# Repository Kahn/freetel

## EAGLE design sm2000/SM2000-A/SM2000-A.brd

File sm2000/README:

README for SM1000 Project
Rick Barnich KA8BMA and David Rowe VK5DGR 
Created 14 August 2014

Introduction
------------

The SM1000 is an embedded hardware product that allows you to run
FreeDV without a PC. Just plug it into your SSB or FM radio, and you
now have Digital Voice (DV). It’s based on a STM32F4 micro-controller,
has a built in microphone, speaker amplifier, and transformer isolated
interfaces to your radio. It’s about the size of a smart phone, and
can be held in you hand and used like a regular PTT microphone, or sit
near your radio in a small box. SmartMic is slated for production
production in 2014 and will retail for US$195.

The SM1000 is open hardware (TAPR license) and runs open software
(LGPL license).

Notes
------

The original name for the project was SmartMic.  However as this name
is tradmarked in the USA we are now calling the project "the
SM1000".

The SM1000 schematic and PCB are design using Eagle.

The firmware lives in codec-dev/stm32.

Directories
-----------

doc         Documentation, use cases, block diagram, prototype assembly images
SM1000-A    First pass design that was never manufactured but used to collect
            review comment
SM1000-B    Prototype SM1000, small qty of PCBs made and hand loaded
SM1000-C    pre-Beta SM1000. Changes to B to reflect testing / debug process.
            Just 2 made to check changes before Qty 100 beta run.
SM1000-D    Beta SM1000

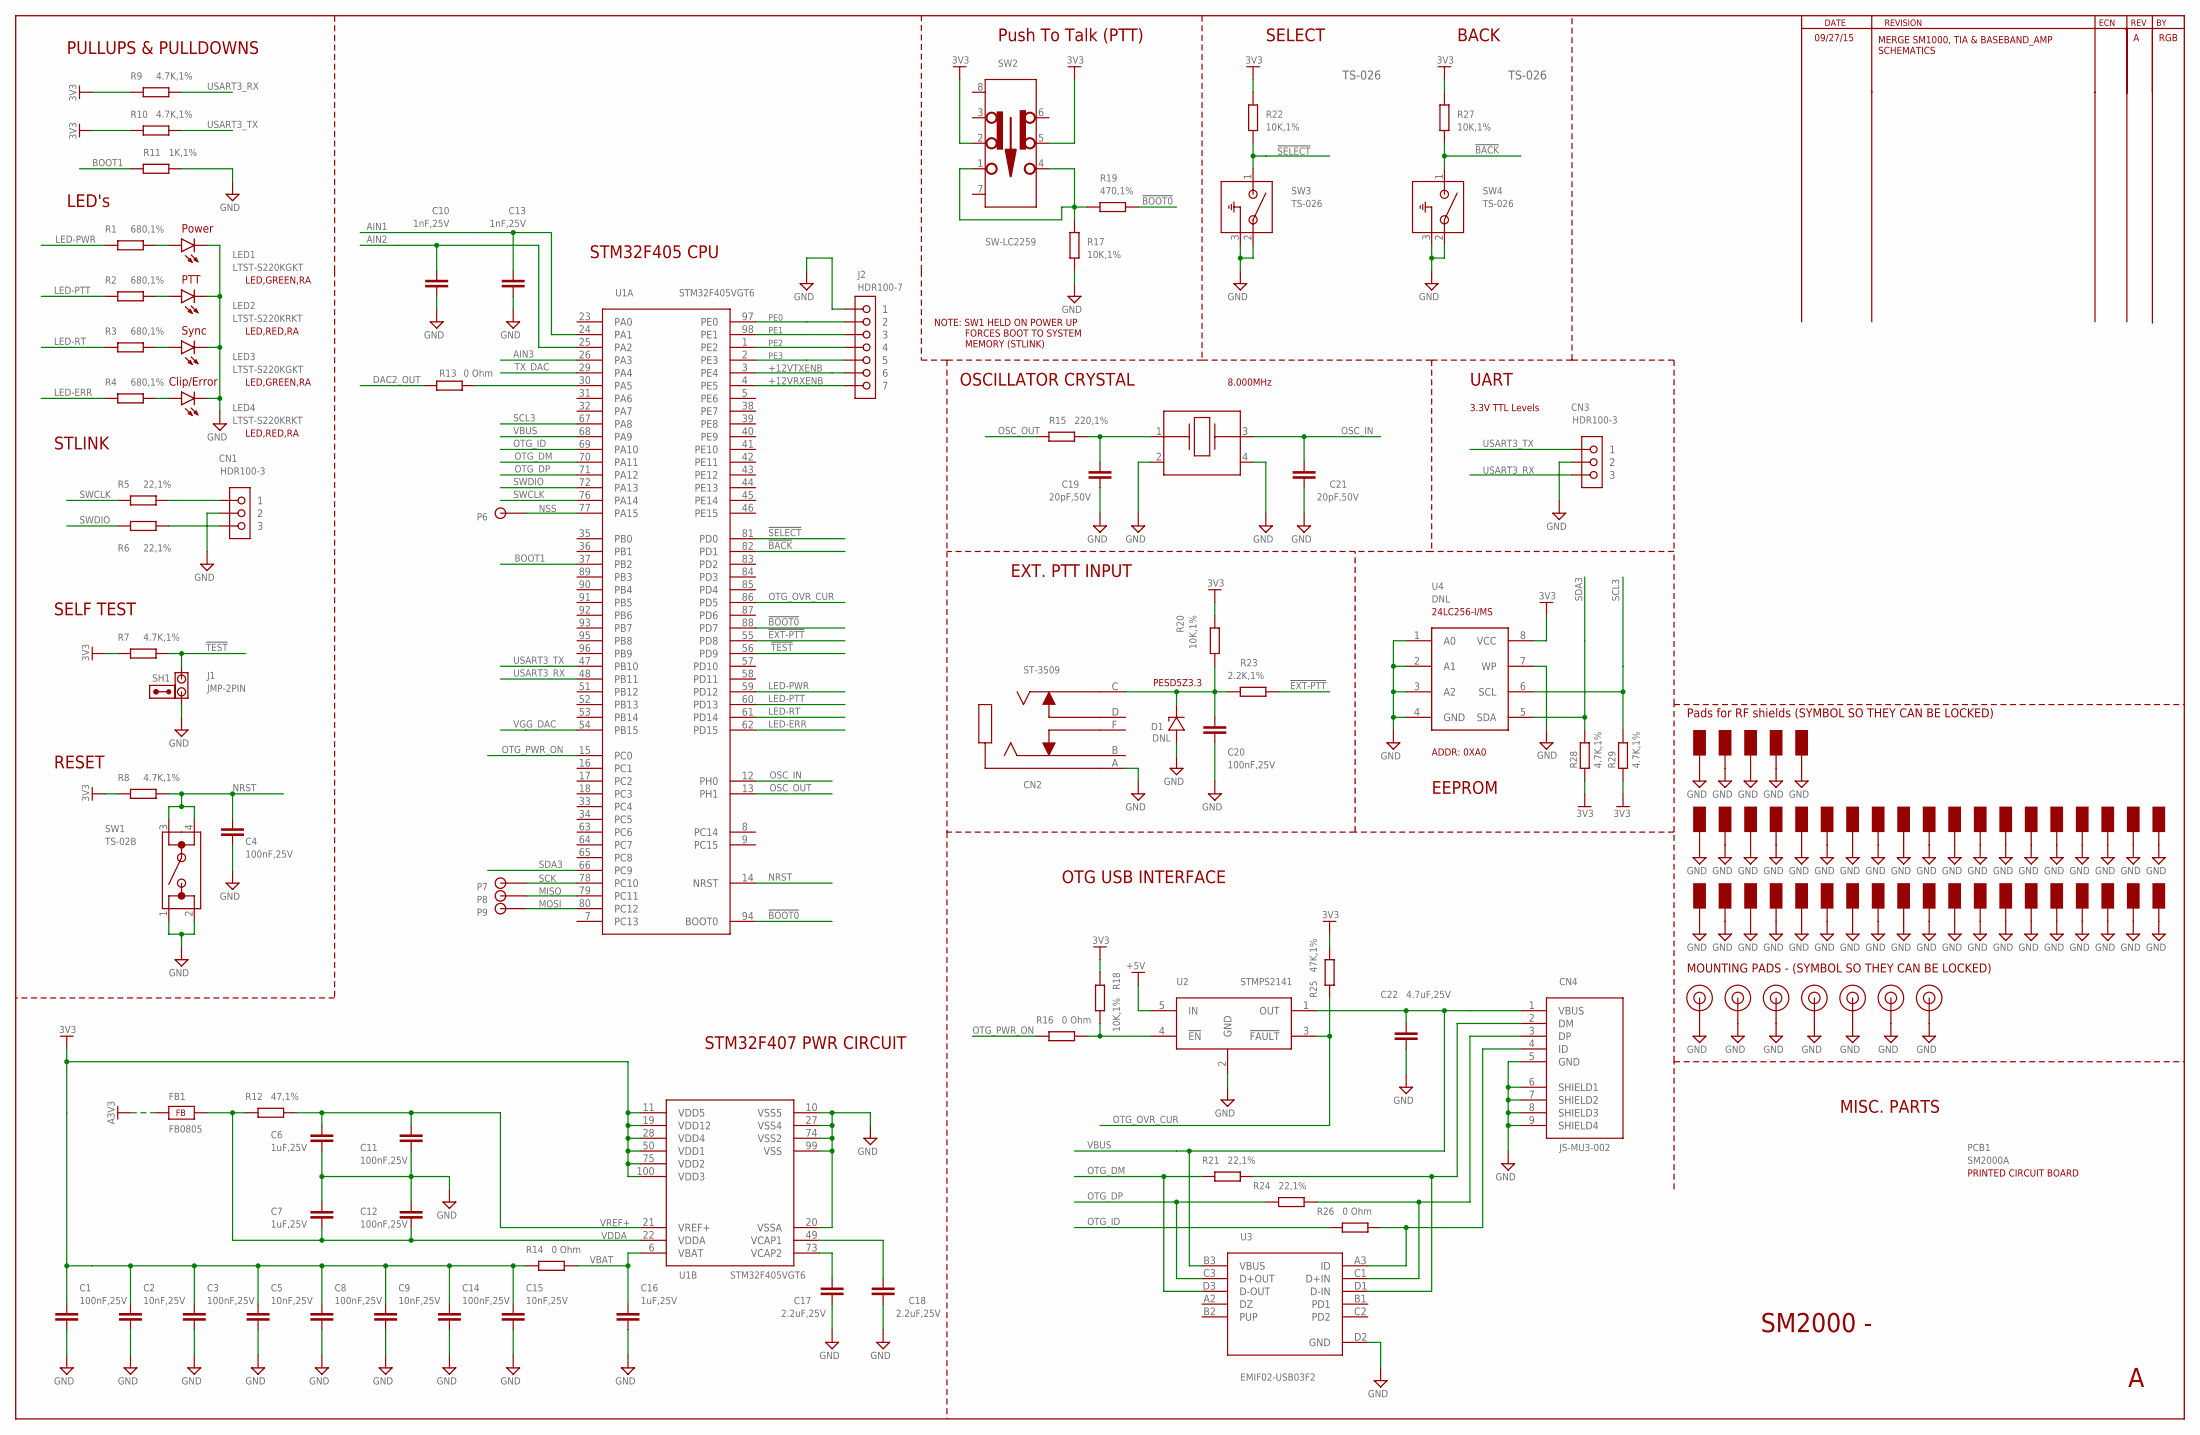
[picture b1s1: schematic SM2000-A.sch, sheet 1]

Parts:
C1, C3, C4, C8, C11, C12, C14, C20: 100nF,25V; C0805
C2, C5, C9, C15: 10nF,25V; C0805
C6, C7, C16: 1uF,25V; C0805
C10, C13: 1nF,25V; C0805
C17, C18: 2.2uF,25V; C0805
C19, C21: 20pF,50V; C0805
C22: 4.7uF,25V; C0805
CN1, CN3: HDR100-3
CN2: ST-3509
CN4: JS-MU3-002; JI-MU3-002
D1: DNL; SOD523
FB1: FB0805; FE0805
J1: JMP-2PIN; JMPR-2PIN
J2: HDR100-7
LED1, LED3: LTST-S220KGKT; LTST-S2200K
LED2, LED4: LTST-S220KRKT; LTST-S2200K
P6, P7, P8, P9: TPAD50
PAD1, PAD2, PAD3, PAD4, PAD5, PAD6, PAD7: MTG-PAD-3.2
PCB1: SM2000A; NOPACKAGE
R1, R2, R3, R4: 680,1%; R0805
R5, R6, R21, R24: 22,1%; R0805
R7, R8, R9, R10, R28, R29: 4.7K,1%; R0805
R11: 1K,1%; R0805
R12: 47,1%; R0805
R13, R14, R16, R26: 0 Ohm; R0805
R15: 220,1%; R0805
R17, R18, R20, R22, R27: 10K,1%; R0805
R19: 470,1%; R0805
R23: 2.2K,1%; R0805
R25: 47K,1%; R0805
S1, S2, S3, S4, S5, S6, S7, S8, S9, S10, S11, S12, S13, S14, S15, S16, S17, S18, S19, S20, S21, S22, S23, S24, S25, S26, S27, S28, S29, S30, S31, S32, S33, S34, S35, S36, S37, S38, S39, S40, S41, S42, S43: SGND
SH1: SHUNT,0.1IN; NOPACKAGE
SW1: TS-02B
SW2: SW-LC2259
SW3, SW4: TS-026
U1: STM32F405VGT6; LQFP100-14
U2: STMPS2141; SOT23-5L
U3: EMIF02-USB03F2; ECOPACK-11
U4: DNL; SOIC8
XTAL1: 8.000MHz; CTS-405

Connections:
3V3: C1.1, C2.1, C3.1, C5.1, C8.1, C9.1, C14.1, C15.1, R7.1, R8.1, R9.1, R10.1, R14.1, R18.2, R20.1, R22.2, R25.1, R27.2, R28.1, R29.1, SW2.2, SW2.5, U1.11 (VDD5), U1.19 (VDD12), U1.28 (VDD4), U1.50 (VDD1), U1.75 (VDD2), U1.100 (VDD3), U4.8 (VCC); also elsewhere on the board
!BACK!: R27.1, SW4.1, U1.82 (PD1)
!BOOT0!: R19.1, U1.88 (PD7), U1.94 (BOOT0)
!EXT-PTT!: R23.2, U1.55 (PD8)
!SELECT!: R22.1, SW3.1, U1.81 (PD0)
!TEST!: J1.1, R7.2, U1.56 (PD9)
+5V: U2.5 (IN); also elsewhere on the board
+12VRXENB: J2.7, U1.4 (PE5); also elsewhere on the board
+12VTXENB: J2.6, U1.3 (PE4); also elsewhere on the board
A3V3: FB1.1; also elsewhere on the board
AIN1: C13.1, U1.24 (PA1); also elsewhere on the board
AIN2: C10.1, U1.25 (PA2); also elsewhere on the board
AIN3: U1.26 (PA3); also elsewhere on the board
BOOT1: R11.2, U1.37 (PB2)
DAC2_OUT: R13.2; also elsewhere on the board
GND: C1.2, C2.2, C3.2, C4.2, C5.2, C6.2, C7.2, C8.2, C9.2, C10.2, C11.2, C12.2, C13.2, C14.2, C15.2, C16.2, C17.2, C18.2, C19.2, C20.2, C21.2, C22.2, CN1.2, CN2.A, CN3.2, CN4.5 (GND), CN4.6 (SHIELD1), CN4.7 (SHIELD2), CN4.8 (SHIELD3), CN4.9 (SHIELD4), D1.A, J1.2, J2.1, LED1.C, LED2.C, LED3.C, LED4.C, PAD1.P$1, PAD2.P$1, PAD3.P$1, PAD4.P$1, PAD5.P$1, PAD6.P$1, PAD7.P$1, R11.1, R17.1, S1.1, S2.1, S3.1, S4.1, S5.1, S6.1, S7.1, S8.1, S9.1, S10.1, S11.1, S12.1, S13.1, S14.1, S15.1, S16.1, S17.1, S18.1, S19.1, S20.1, S21.1, S22.1, S23.1, S24.1, S25.1, S26.1, S27.1, S28.1, S29.1, S30.1, S31.1, S32.1, S33.1, S34.1, S35.1, S36.1, S37.1, S38.1, S39.1, S40.1, S41.1, S42.1, S43.1, SW1.1, SW1.2, SW3.2, SW3.3, SW4.2, SW4.3, U1.10 (VSS5), U1.20 (VSSA), U1.27 (VSS4), U1.74 (VSS2), U1.99 (VSS), U2.2 (GND), U3.D2 (GND), U4.1 (A0), U4.2 (A1), U4.3 (A2), U4.4 (GND), U4.7 (WP), XTAL1.2, XTAL1.4; also elsewhere on the board
LED-ERR: R4.1, U1.62 (PD15)
LED-PTT: R2.1, U1.60 (PD13)
LED-PWR: R1.1, U1.59 (PD12)
LED-RT: R3.1, U1.61 (PD14)
MISO: P8.1, U1.79 (PC11)
MOSI: P9.1, U1.80 (PC12)
unnamed: C17.1, U1.73 (VCAP2)
unnamed: C18.1, U1.49 (VCAP1)
unnamed: CN1.3, R6.2
unnamed: CN1.1, R5.2
unnamed: C19.1, R15.2, XTAL1.1
unnamed: R13.1, U1.30 (PA5)
unnamed: R17.2, R19.2, SW2.1, SW2.4
unnamed: C20.1, CN2.C, D1.C, R20.2, R23.1
unnamed: LED1.A, R1.2
unnamed: LED2.A, R2.2
unnamed: LED3.A, R3.2
unnamed: LED4.A, R4.2
unnamed: CN4.3 (DP), R24.1, U3.C1 (D+IN)
unnamed: CN4.2 (DM), R21.1, U3.D1 (D-IN)
unnamed: CN4.4 (ID), R26.1, U3.A3 (ID)
unnamed: R16.2, R18.1, U2.4 (!EN!)
NRST: C4.1, R8.2, SW1.3, SW1.4, U1.14 (NRST)
NSS: P6.1, U1.77 (PA15)
OSC_IN: C21.1, U1.12 (PH0), XTAL1.3
OSC_OUT: R15.1, U1.13 (PH1)
OTG_DM: R21.2, U1.70 (PA11), U3.D3 (D-OUT)
OTG_DP: R24.2, U1.71 (PA12), U3.C3 (D+OUT)
OTG_ID: R26.2, U1.69 (PA10)
OTG_OVR_CUR: R25.2, U1.86 (PD5), U2.3 (!FAULT!)
OTG_PWR_ON: R16.1, U1.15 (PC0)
PE0: J2.2, U1.97 (PE0)
PE1: J2.3, U1.98 (PE1)
PE2: J2.4, U1.1 (PE2)
PE3: J2.5, U1.2 (PE3)
SCK: P7.1, U1.78 (PC10)
SCL3: R29.2, U1.67 (PA8), U4.6 (SCL); also elsewhere on the board
SDA3: R28.2, U1.66 (PC9), U4.5 (SDA); also elsewhere on the board
SWCLK: R5.1, U1.76 (PA14)
SWDIO: R6.1, U1.72 (PA13)
TX_DAC: U1.29 (PA4); also elsewhere on the board
USART3_RX: CN3.3, R9.2, U1.48 (PB11)
USART3_TX: CN3.1, R10.2, U1.47 (PB10)
VBAT: C16.1, R14.2, U1.6 (VBAT)
VBUS: C22.1, CN4.1 (VBUS), U1.68 (PA9), U2.1 (OUT), U3.B3 (VBUS)
VDDA: C7.1, C12.1, FB1.2, R12.1, U1.22 (VDDA)
VGG_DAC: U1.54 (PB15); also elsewhere on the board
VREF+: C6.1, C11.1, R12.2, U1.21 (VREF+)

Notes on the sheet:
PULLUPS & PULLDOWNS
LED's
STLINK
OSCILLATOR CRYSTAL
OTG USB INTERFACE
STM32F405 CPU
STM32F407 PWR CIRCUIT
SM2000 -
Push To Talk (PTT)
NOTE: SW1 HELD ON POWER UP FORCES BOOT TO SYSTEM MEMORY (STLINK)
SELF TEST
RESET
SELECT
BACK
Power
PTT
Sync
Clip/Error
UART
3.3V TTL Levels
8.000MHz
TS-026
RGB
MISC. PARTS
LED,GREEN,RA
LED,RED,RA
EEPROM
ADDR: 0XA0
09/27/15
24LC256-I/MS
MERGE SM1000, TIA & BASEBAND_AMP SCHEMATICS
EXT. PTT INPUT
PESD5Z3.3
Pads for RF shields (SYMBOL SO THEY CAN BE LOCKED)
MOUNTING PADS - (SYMBOL SO THEY CAN BE LOCKED)

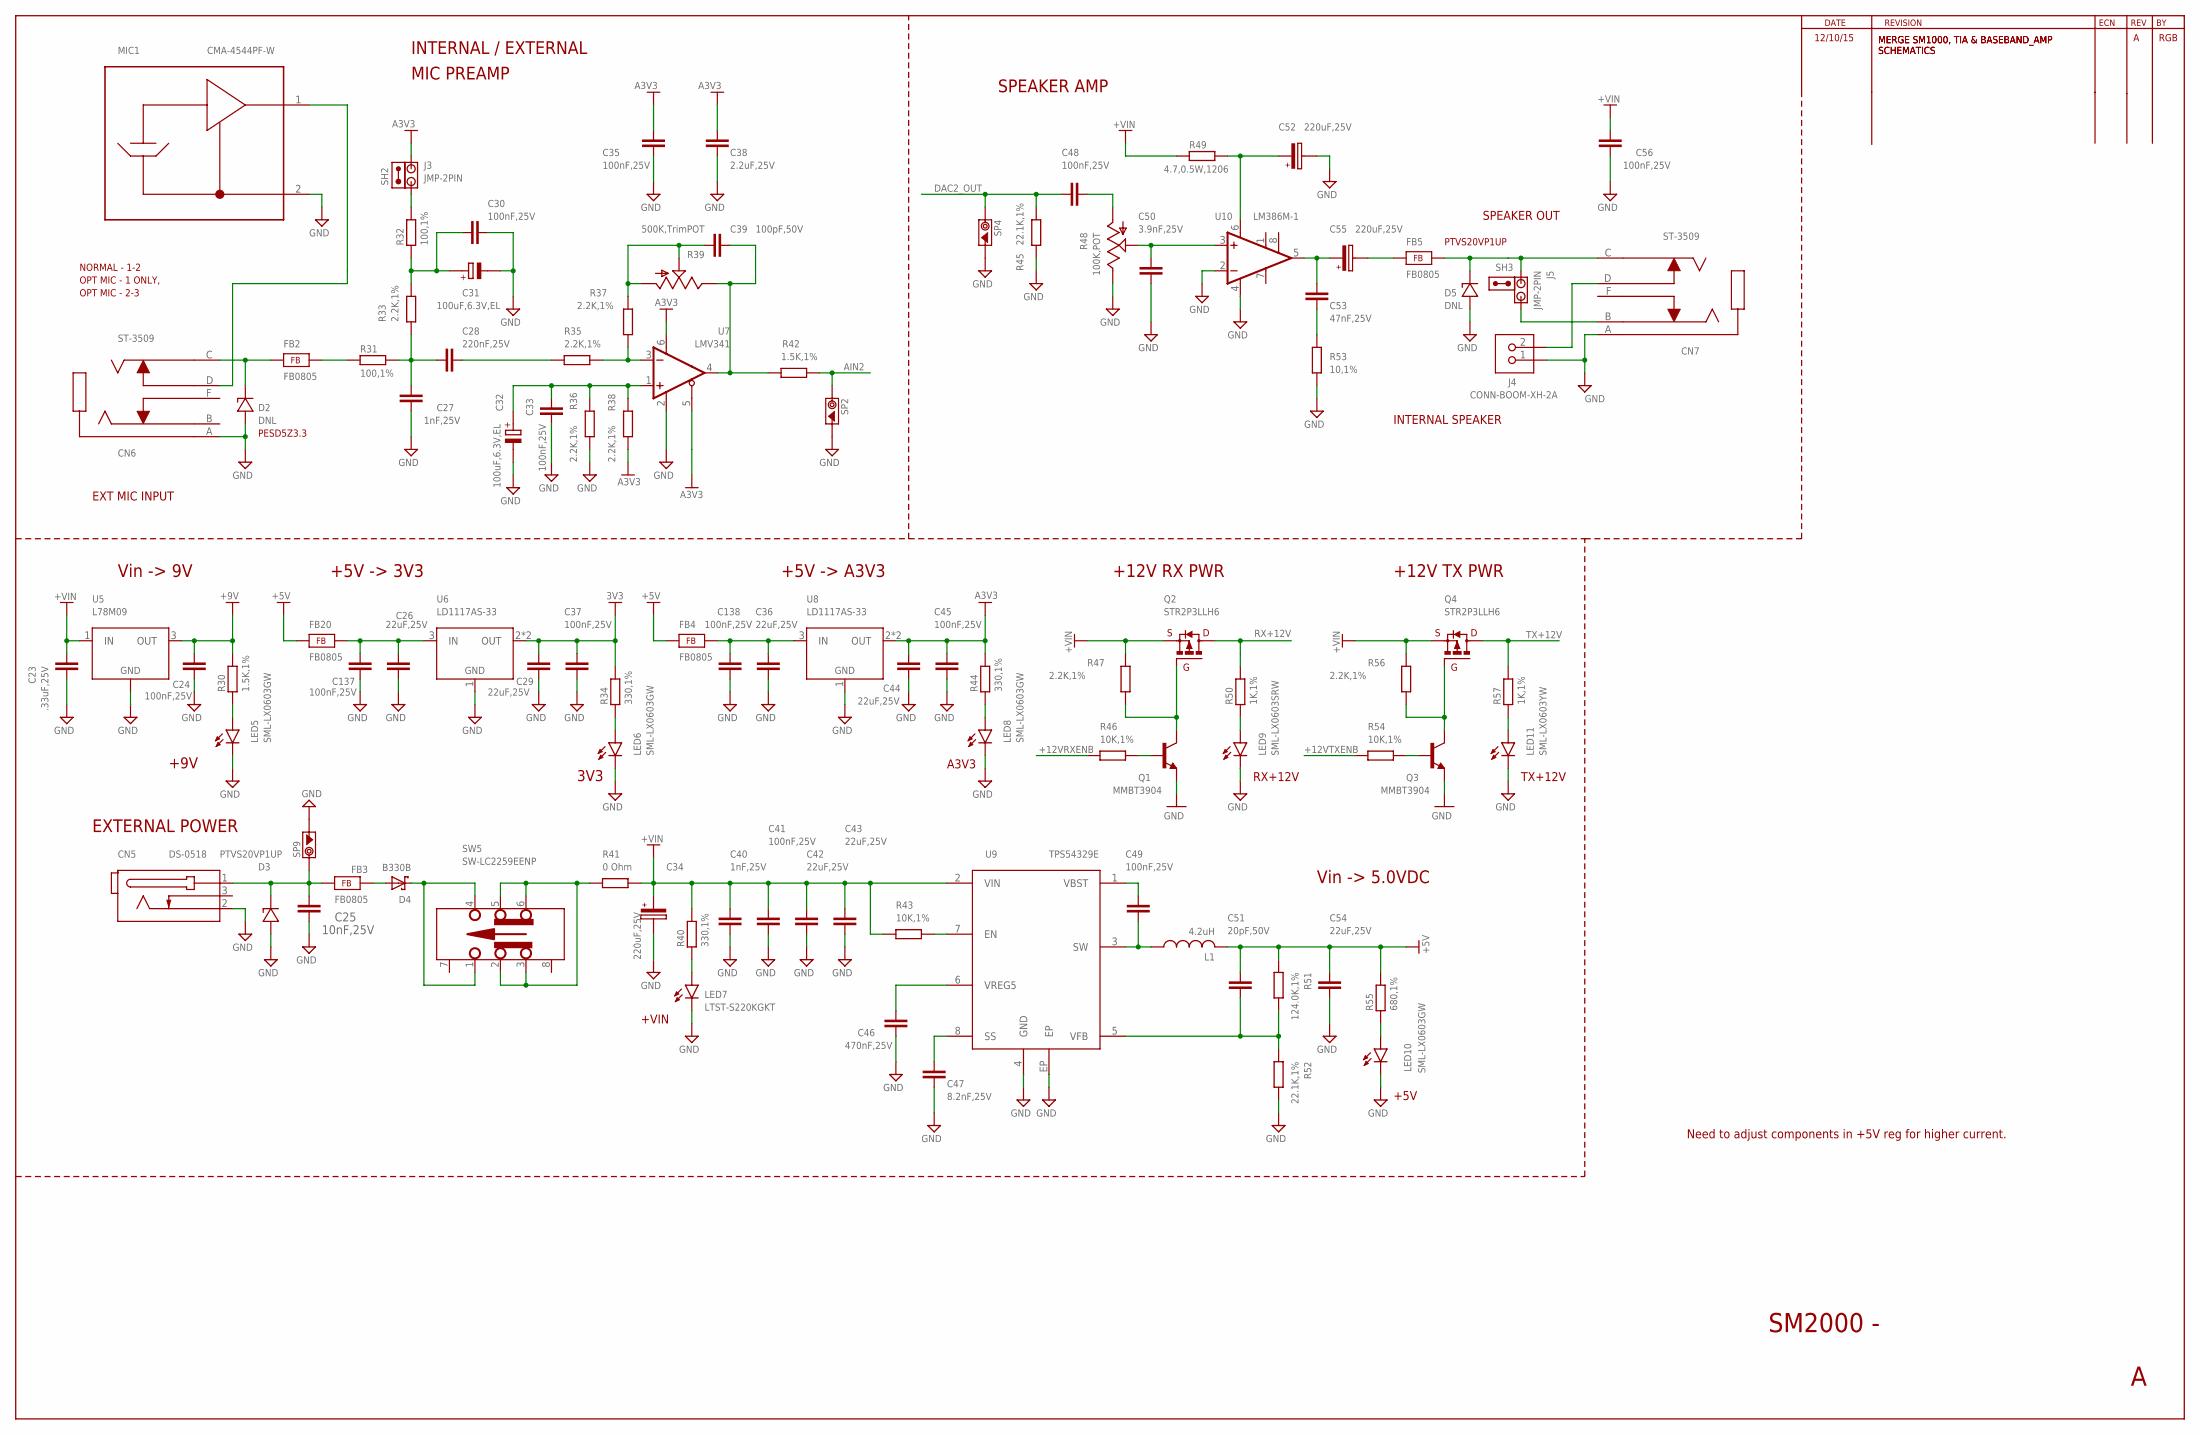
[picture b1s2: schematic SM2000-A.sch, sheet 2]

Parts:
C23: .33uF,25V; C0805
C24, C30, C33, C35, C37, C41, C45, C48, C49, C56, C137, C138: 100nF,25V; C0805
C25: 10nF,25V; C0805
C26, C29, C36, C42, C43, C44, C54: 22uF,25V; C1210
C27, C40: 1nF,25V; C0805
C28: 220nF,25V; C0805
C31, C32: 100uF,6.3V,EL; NICHICON-WX-6.3
C34, C52, C55: 220uF,25V; CAP-CHEMI-HA0
C38: 2.2uF,25V; C0805
C39: 100pF,50V; C0805
C46: 470nF,25V; C0805
C47: 8.2nF,25V; C0805
C50: 3.9nF,25V; C0805
C51: 20pF,50V; C0805
C53: 47nF,25V; C0805
CN5: DS-0518
CN6, CN7: ST-3509
D2: DNL; SOD523
D3: PTVS20VP1UP; SOD128
D4: B330B; SMB
D5: DNL; SOD128
FB2, FB3, FB4, FB5, FB20: FB0805; FE0805
J3, J5: JMP-2PIN; JMPR-2PIN
J4: CONN-BOOM-XH-2A
L1: 4.2uH; SRR5028
LED5, LED6, LED8, LED10: SML-LX0603GW; SML-LX0603SRW
LED7: LTST-S220KGKT; LTST-S2200K
LED9: SML-LX0603SRW
LED11: SML-LX0603YW; SML-LX0603SRW
MIC1: CMA-4544PF-W
Q1, Q3: MMBT3904; SOT23
Q2, Q4: STR2P3LLH6; SOT23
R30, R42: 1.5K,1%; R0805
R31, R32: 100,1%; R0805
R33, R35, R36, R37, R38, R47, R56: 2.2K,1%; R0805
R34, R40, R44: 330,1%; R0805
R39: 500K,TrimPOT; POT3361
R41: 0 Ohm; R0805
R43, R46, R54: 10K,1%; R0805
R45, R52: 22.1K,1%; R0805
R48: 100K,POT; POT-3310C
R49: 4.7,0.5W,1206; R1206
R50, R57: 1K,1%; R0805
R51: 124.0K,1%; R0805
R53: 10,1%; R0805
R55: 680,1%; R0805
SH2, SH3: SHUNT,0.1IN; NOPACKAGE
SP2, SP4, SP9: SCOPE_PAD
SW5: SW-LC2259EENP; SW-LC2259
U5: L78M09; DPAK
U6, U8: LD1117AS-33; SOT223
U7: LMV341; SOT23-6
U9: TPS54329E; PSO-DDA
U10: LM386M-1; SO08

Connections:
3V3: C29.1, C37.1, R34.2, U6.2 (OUT), U6.4 (OUT); also elsewhere on the board
+5V: C51.1, C54.1, FB4.1, FB20.1, L1.2, R51.1, R55.2; also elsewhere on the board
+9V: C24.1, R30.2, U5.3 (OUT); also elsewhere on the board
+12VRXENB: R46.1; also elsewhere on the board
+12VTXENB: R54.1; also elsewhere on the board
+VIN: C23.1, C34.1, C40.1, C41.1, C42.1, C43.1, C56.1, Q2.2 (S), Q4.2 (S), R40.2, R41.2, R43.1, R47.2, R49.1, R56.2, U5.1 (IN), U9.2 (VIN)
A3V3: C35.1, C38.1, C44.1, C45.1, J3.2, R38.2, R44.2, U7.5 (!SHDN!), U7.6 (V+), U8.2 (OUT), U8.4 (OUT); also elsewhere on the board
AIN2: R42.1, SP2.1; also elsewhere on the board
DAC2_OUT: C48.1, R45.1, SP4.1; also elsewhere on the board
GND: C23.2, C24.2, C25.2, C26.2, C27.2, C29.2, C30.2, C31.2 (-), C32.2 (-), C33.1, C34.2, C35.2, C36.2, C37.2, C38.2, C40.2, C41.2, C42.2, C43.2, C44.2, C45.2, C46.2, C47.2, C50.2, C52.2, C54.2, C56.2, C137.2, C138.2, CN5.2, CN6.A, CN7.A, D2.A, D3.A, D5.A, J4.1, LED5.C, LED6.C, LED7.C, LED8.C, LED9.C, LED10.C, LED11.C, MIC1.2, Q1.2 (E), Q3.2 (E), R36.2, R45.2, R48.1, R52.2, R53.2, SP2.2, SP4.2, SP9.2, U5.4 (GND), U6.1 (GND), U7.2 (GND), U8.1 (GND), U9.4 (GND), U9.EP, U10.2 (-IN), U10.4 (GND); also elsewhere on the board
unnamed: C53.1, C55.1, U10.5 (OUT)
unnamed: D4.A, FB3.2
unnamed: C27.1, C28.1, R31.2, R33.1
unnamed: FB2.2, R31.1
unnamed: C39.2, R39.1, R42.2, U7.4 (OUT)
unnamed: J3.1, R32.2
unnamed: C48.2, R48.3
unnamed: C28.2, R35.1
unnamed: C50.1, R48.2, U10.3 (+IN)
unnamed: C39.1, R37.2, R39.2, R39.3
unnamed: Q1.3 (C), Q2.1 (G), R47.1
unnamed: C53.2, R53.1
unnamed: C55.2, FB5.1
unnamed: C30.1, C31.1 (+), R32.1, R33.2
unnamed: C32.1 (+), C33.2, R36.1, R38.1, U7.1 (+IN)
unnamed: C52.1, R49.2, U10.6 (VS)
unnamed: Q3.3 (C), Q4.1 (G), R56.1
unnamed: Q1.1 (B), R46.2
unnamed: C36.1, C138.1, FB4.2, U8.3 (IN)
unnamed: Q3.1 (B), R54.2
unnamed: CN6.D, MIC1.1
unnamed: CN7.C, D5.C, FB5.2, J5.2
unnamed: LED5.A, R30.1
unnamed: CN7.B, J5.1
unnamed: CN7.D, J4.2
unnamed: CN6.C, D2.C, FB2.1
unnamed: C25.1, CN5.1, D3.C, FB3.1, SP9.1
unnamed: D4.C (K), SW5.1, SW5.4
unnamed: R35.2, R37.1, U7.3 (-IN)
unnamed: C26.1, C137.1, FB20.2, U6.3 (IN)
unnamed: LED8.A, R44.1
unnamed: LED9.A, R50.1
unnamed: LED6.A, R34.1
unnamed: LED11.A, R57.1
unnamed: LED10.A, R55.1
unnamed: LED7.A, R40.1
unnamed: R41.1, SW5.2, SW5.3, SW5.5, SW5.6
unnamed: C49.1, U9.1 (VBST)
unnamed: C51.2, R51.2, R52.1, U9.5 (VFB)
unnamed: C47.1, U9.8 (SS)
unnamed: C46.1, U9.6 (VREG5)
unnamed: R43.2, U9.7 (EN)
RX+12V: Q2.3 (D), R50.2; also elsewhere on the board
SW: C49.2, L1.1, U9.3 (SW)
TX+12V: Q4.3 (D), R57.2; also elsewhere on the board

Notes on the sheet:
SPEAKER OUT
EXT MIC INPUT
EXTERNAL POWER
INTERNAL / EXTERNAL
MIC PREAMP
SPEAKER AMP
SM2000 -
NORMAL - 1-2
OPT MIC - 1 ONLY,
OPT MIC - 2-3
INTERNAL SPEAKER
+5V -> A3V3
PTVS20VP1UP
PESD5Z3.3
RGB
12/10/15
MERGE SM1000, TIA & BASEBAND_AMP SCHEMATICS
+12V RX PWR
+12V TX PWR
Vin -> 5.0VDC
+5V -> 3V3
Vin -> 9V
Need to adjust components in +5V reg for higher current.
+9V
3V3
A3V3
RX+12V
TX+12V
+5V
+VIN

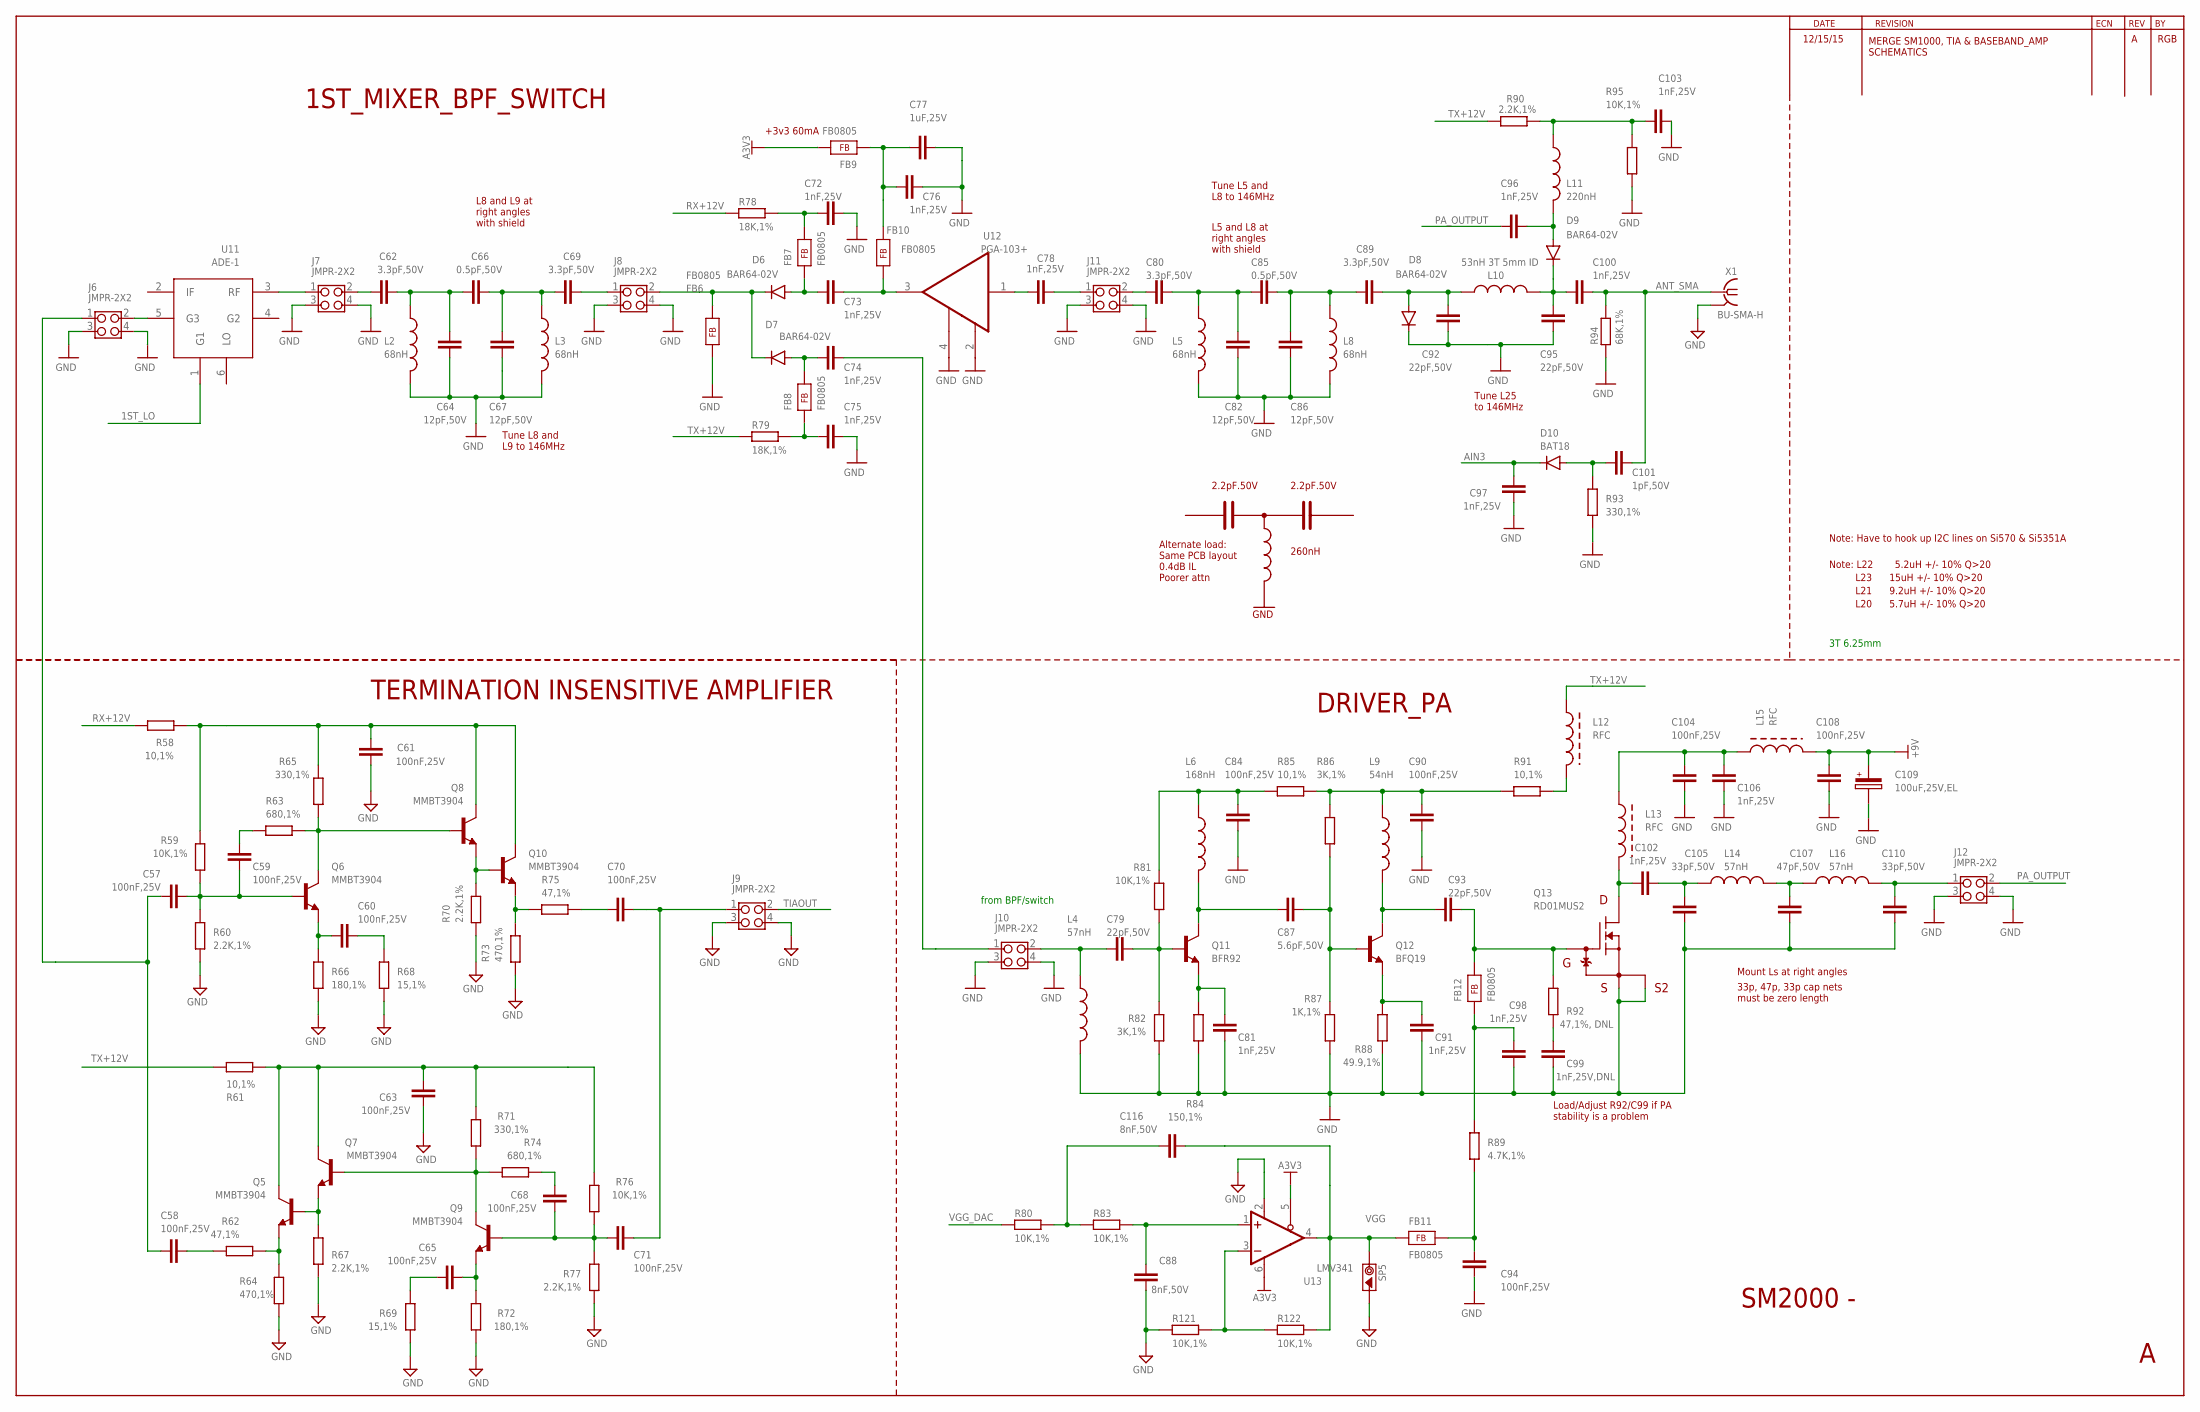
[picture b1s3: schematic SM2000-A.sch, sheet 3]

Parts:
C57, C58, C59, C60, C61, C63, C65, C68, C70, C71, C84, C90, C94, C104, C108: 100nF,25V; C0805
C62, C69, C80, C89: 3.3pF,50V; C0805
C64, C67, C82, C86: 12pF,50V; C0805
C66, C85: 0.5pF,50V; C0805
C72, C73, C74, C75, C76, C78, C81, C91, C96, C97, C98, C100, C102, C103, C106: 1nF,25V; C0805
C77: 1uF,25V; C0805
C79, C92, C93, C95: 22pF,50V; C0805
C87: 5.6pF,50V; C0805
C88, C116: 8nF,50V; C0805
C99: 1nF,25V,DNL; C0805
C101: 1pF,50V; C0805
C105, C110: 33pF,50V; C0805
C107: 47pF,50V; C0805
C109: 100uF,25V,EL; CAP-CHEMI-F80
D6, D7, D8, D9: BAR64-02V; SC79_INFINEON
D10: BAT18; SOT23
FB6, FB7, FB8, FB9, FB10, FB11, FB12: FB0805; FE0805
J6, J7, J8, J9, J10, J11, J12: JMPR-2X2; JMPR-2X2X.1
L2, L3, L5, L8: 68nH; L10X15
L4, L14, L16: 57nH; L10X15
L6: 168nH; L10X15
L9: 54nH; L10X15
L10: 53nH 3T 5mm ID; L10X15
L11: 220nH; L10X15
L12, L13, L15: RFC; Z15/4
Q5, Q6, Q7, Q8, Q9, Q10: MMBT3904; SOT23
Q11: BFR92; SOT23
Q12: BFQ19; SOT89
Q13: RD01MUS2; SOT89
R58, R61, R85, R91: 10,1%; R0805
R59, R76, R80, R81, R83, R95, R121, R122: 10K,1%; R0805
R60, R67, R70, R77, R90: 2.2K,1%; R0805
R62, R75: 47,1%; R0805
R63, R74: 680,1%; R0805
R64, R73: 470,1%; R0805
R65, R71, R93: 330,1%; R0805
R66, R72: 180,1%; R0805
R68, R69: 15,1%; R0805
R78, R79: 18K,1%; R0805
R82, R86: 3K,1%; R0805
R84: 150,1%; R0805
R87: 1K,1%; R0805
R88: 49.9,1%; R0805
R89: 4.7K,1%; R0805
R92: 47,1%, DNL; R0805
R94: 68K,1%; R0805
SP5: SCOPE_PAD
U11: ADE-1
U12: PGA-103+; DF782
U13: LMV341; SOT23-6
X1: BU-SMA-H

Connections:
1ST_LO: U11.1 (G1); also elsewhere on the board
+9V: C108.1, C109.1, L15.2; also elsewhere on the board
A3V3: FB9.2, U13.5 (!SHDN!), U13.6 (V+); also elsewhere on the board
AIN3: C97.2, D10.1 (K); also elsewhere on the board
ANT_SMA: C100.1, C101.2, R94.2, X1.1
DRIVER/PA_INPUT: C74.2, J10.1
GND: C61.2, C63.2, C64.2, C67.1, C72.2, C75.2, C76.2, C77.2, C81.2, C82.2, C84.2, C86.1, C88.2, C90.2, C91.2, C92.2, C94.2, C95.2, C97.1, C98.2, C99.2, C103.2, C104.2, C105.2, C106.2, C107.2, C108.2, C109.2, C110.2, D8.C, FB6.1, J6.3, J6.4, J7.3, J7.4, J8.3, J8.4, J9.3, J9.4, J10.3, J10.4, J11.3, J11.4, J12.3, J12.4, L2.2, L3.2, L4.2, L5.2, L8.2, Q13.2 (S), Q13.4 (S2), R60.1, R64.1, R66.1, R67.1, R68.1, R69.1, R70.1, R72.1, R73.1, R77.1, R82.1, R84.1, R87.1, R88.1, R93.1, R94.1, R95.1, R121.1, SP5.2, U12.2 (GND), U12.4 (GND1), U13.2 (GND), X1.2, X1.3 (2), X1.4 (2), X1.5 (2); also elsewhere on the board
unnamed: C76.1, C77.1, FB9.1, FB10.2
unnamed: R121.2, R122.1, U13.3 (-IN)
unnamed: C107.1, L14.2, L16.1
unnamed: C80.2, J11.2
unnamed: L12.2, R91.1
unnamed: C62.1, C64.1, C66.2, L2.1
unnamed: C116.1, R80.2, R83.1
unnamed: C102.1, L13.2, Q13.3 (D)
unnamed: C93.1, FB12.2, Q13.1 (G), R92.2
unnamed: C88.1, R83.2, U13.1 (+IN)
unnamed: C95.1, C100.2, D9.C, L10.2
unnamed: C94.1, FB11.2, R89.1
unnamed: C110.1, J12.1, L16.2
unnamed: C62.2, J7.2
unnamed: C101.1, D10.3 (A), R93.2
unnamed: J7.1, U11.3 (RF)
unnamed: C78.2, J11.1
unnamed: C78.1, U12.1 (1N)
unnamed: Q6.3 (C), Q8.1 (B), R63.2, R65.2
unnamed: C61.1, Q8.3 (C), Q10.3 (C), R58.1, R59.2, R65.1
unnamed: Q8.2 (E), Q10.1 (B), R70.2
unnamed: C59.1, R63.1
unnamed: C81.1, Q11.2 (E), R84.2
unnamed: C91.1, Q12.3 (E), R88.2
unnamed: C84.1, L6.1, R81.2, R85.2
unnamed: C90.1, L9.1, R85.1, R86.2, R91.2
unnamed: C87.1, Q12.1 (B), R86.1, R87.2
unnamed: C79.1, Q11.1 (B), R81.1, R82.2
unnamed: C69.1, J8.1
unnamed: C87.2, L6.2, Q11.3 (C)
unnamed: C57.1, C59.2, Q6.1 (B), R59.1, R60.2
unnamed: C93.2, L9.2, Q12.2 (C), Q12.4 (C)
unnamed: C60.1, Q6.2 (E), R66.2
unnamed: C60.2, R68.2
unnamed: Q10.2 (E), R73.2, R75.1
unnamed: C70.2, R75.2
unnamed: J6.2, U11.5 (G3)
unnamed: Q7.1 (B), Q9.3 (C), R71.2, R74.2
unnamed: C63.1, Q5.3 (C), Q7.3 (C), R61.2, R71.1, R76.2
unnamed: Q5.1 (B), Q7.2 (E), R67.2
unnamed: C68.1, R74.1
unnamed: C68.2, C71.1, Q9.1 (B), R76.1, R77.2
unnamed: C65.1, Q9.2 (E), R72.2
unnamed: C65.2, R69.2
unnamed: Q5.2 (E), R62.1, R64.2
unnamed: C58.2, R62.2
unnamed: C72.1, FB7.2, R78.2
unnamed: C79.2, J10.2, L4.1
unnamed: C99.1, R92.1
unnamed: C98.1, FB12.1, R89.2
unnamed: C73.1, D6.A, FB7.1
unnamed: C73.2, FB10.1, U12.3 (OUT)
unnamed: C74.1, D7.A, FB8.2
unnamed: C102.2, C105.1, L14.1
unnamed: C75.1, FB8.1, R79.2
unnamed: C66.1, C67.2, C69.2, L3.1
unnamed: C104.1, C106.1, L13.1, L15.1
unnamed: D6.C, D7.C, FB6.2, J8.2
unnamed: C80.1, C82.1, C85.2, L5.1
unnamed: C85.1, C86.2, C89.2, L8.1
unnamed: C89.1, C92.1, D8.A, L10.1
unnamed: C96.1, D9.A, L11.2
unnamed: C103.1, L11.1, R90.1, R95.2
PA_OUTPUT: C96.2, J12.2
RX+12V: R58.2, R78.1; also elsewhere on the board
TIAIN: C57.2, C58.1, J6.1
TIAOUT: J9.2; also elsewhere on the board
TIA_OUT: C70.1, C71.2, J9.1
TX+12V: L12.1, R61.1, R79.1, R90.2; also elsewhere on the board
VGG: C116.2, FB11.1, R122.2, SP5.1, U13.4 (OUT)
VGG_DAC: R80.1; also elsewhere on the board

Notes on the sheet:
SM2000 -
12/15/15
MERGE SM1000, TIA & BASEBAND_AMP SCHEMATICS
RGB
3T 6.25mm
Note: L22
5.2uH +/- 10% Q>20
L23 15uH +/- 10% Q>20
L21 9.2uH +/- 10% Q>20
L20 5.7uH +/- 10% Q>20
Note: Have to hook up I2C lines on Si570 & Si5351A
Tune L8 and L9 to 146MHz
+3v3 60mA
Alternate load: Same PCB layout 0.4dB IL Poorer attn
Tune L5 and L8 to 146MHz
L5 and L8 at right angles with shield
L8 and L9 at right angles with shield
Tune L25 to 146MHz
1ST_MIXER_BPF_SWITCH
TERMINATION INSENSITIVE AMPLIFIER
Load/Adjust R92/C99 if PA stability is a problem
from BPF/switch
33p, 47p, 33p cap nets must be zero length
Mount Ls at right angles
DRIVER_PA
GND
2.2pF.50V
260nH

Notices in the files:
smartmic/SM1000-F/RELEASE-SM1000-F/SM1000-F.brd:
Copyright 2015
Licensed under TAPR Open Hardware License
parts and their libraries:
A-FRAMES: Copyright 2015 Richard Barnich and David Rowe
A-FRAMES: Licensed Under the TAPR Open Hardware License(www.tapr.org/OHL)
_RoweTel: Copyright 2014  Richard Barnich and David Rowe
